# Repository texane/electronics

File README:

various electronic designs:
. dspic33f_board, a DSPIC33F based board, with CAN transceiver and serial over USB support via FTDI

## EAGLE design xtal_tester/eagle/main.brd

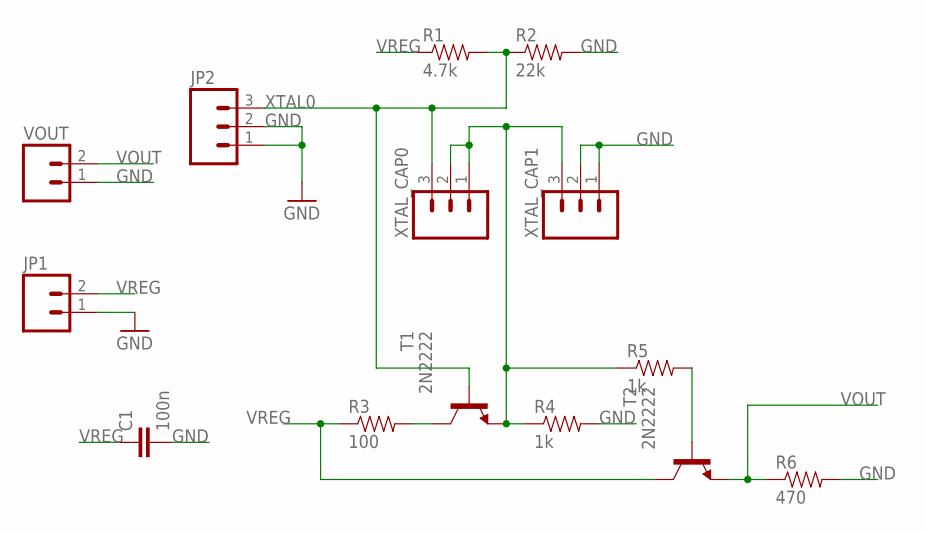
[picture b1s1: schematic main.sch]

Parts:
C1: 100n; CAP-PTH-SMALL
JP1: M02LOCK; 1X02_LOCK
JP2: M03LOCK; 1X03_LOCK
R1: 4.7k; AXIAL-0.4
R2: 22k; AXIAL-0.4
R3: 100; AXIAL-0.4
R4, R5: 1k; AXIAL-0.4
R6: 470; AXIAL-0.4
T1, T2: 2N2222; TO18
VOUT: M02LOCK; 1X02_LOCK
XTAL_CAP0, XTAL_CAP1: M03LOCK; 1X03_LOCK

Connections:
GND: C1.2, JP1.1, JP2.1, JP2.2, R2.P$2 (2), R4.P$2 (2), R6.P$2 (2), VOUT.1, XTAL_CAP1.1, XTAL_CAP1.2
unnamed: R5.P$2 (2), T2.2 (B)
unnamed: R3.P$2 (2), T1.3 (C)
unnamed: R4.P$1 (1), R5.P$1 (1), T1.1 (E), XTAL_CAP0.1, XTAL_CAP0.2, XTAL_CAP1.3
VOUT: R6.P$1 (1), T2.1 (E), VOUT.2
VREG: C1.1, JP1.2, R1.P$1 (1), R3.P$1 (1), T2.3 (C)
XTAL0: JP2.3, R1.P$2 (2), R2.P$1 (1), T1.2 (B), XTAL_CAP0.3

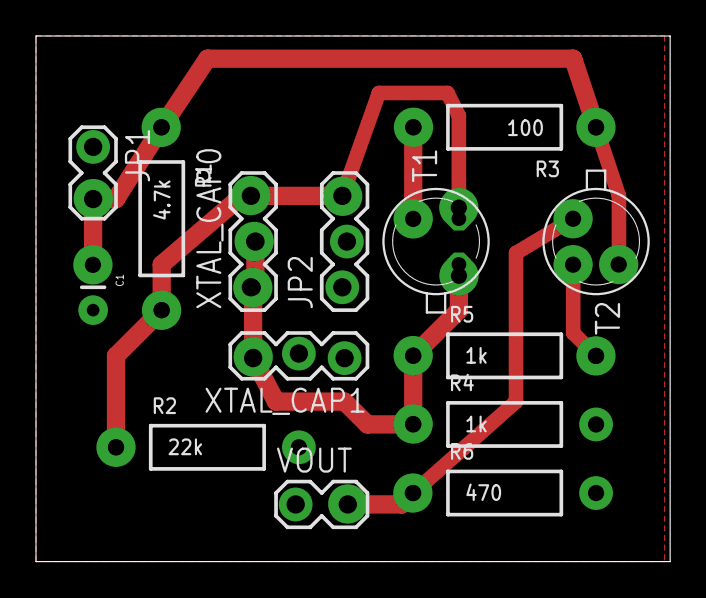
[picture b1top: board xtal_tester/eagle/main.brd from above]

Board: 2 copper layers, 35.2 x 29.2 mm, 14 parts (0 on the bottom side), 7 nets.

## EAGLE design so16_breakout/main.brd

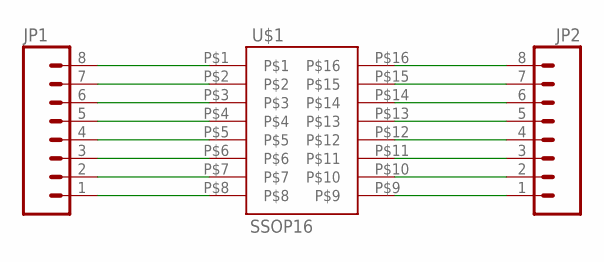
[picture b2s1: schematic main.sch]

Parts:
JP1, JP2: M08LONGPADS; 1X08_LONGPADS
U$1: SSOP16

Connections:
unnamed: JP1.8, U$1.P$1
unnamed: JP1.7, U$1.P$2
unnamed: JP1.6, U$1.P$3
unnamed: JP1.5, U$1.P$4
unnamed: JP1.4, U$1.P$5
unnamed: JP1.3, U$1.P$6
unnamed: JP1.2, U$1.P$7
unnamed: JP1.1, U$1.P$8
unnamed: JP2.8, U$1.P$16
unnamed: JP2.7, U$1.P$15
unnamed: JP2.6, U$1.P$14
unnamed: JP2.5, U$1.P$13
unnamed: JP2.4, U$1.P$12
unnamed: JP2.3, U$1.P$11
unnamed: JP2.2, U$1.P$10
unnamed: JP2.1, U$1.P$9

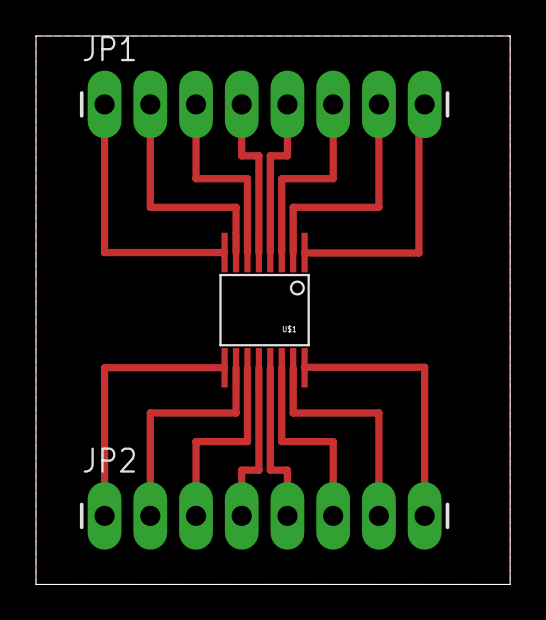
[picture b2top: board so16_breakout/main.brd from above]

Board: 2 copper layers, 26.3 x 30.5 mm, 3 parts (0 on the bottom side), 16 nets.

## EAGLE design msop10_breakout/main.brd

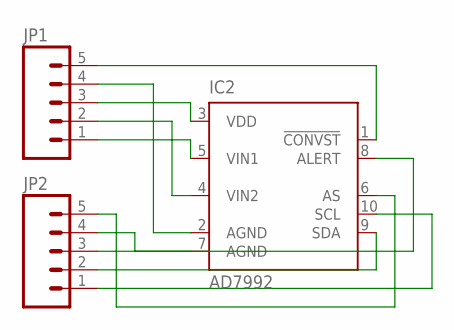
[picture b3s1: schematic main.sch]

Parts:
IC2: AD7992; MSOP10
JP1, JP2: M05PTH_LONGPADS; 1X05_LONGPADS

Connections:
unnamed: IC2.1 (!CONVST), JP1.5
unnamed: IC2.2 (AGND), JP1.4
unnamed: IC2.3 (VDD), JP1.3
unnamed: IC2.4 (VIN2), JP1.2
unnamed: IC2.5 (VIN1), JP1.1
unnamed: IC2.6 (AS), JP2.5
unnamed: IC2.7 (AGND), JP2.4
unnamed: IC2.8 (ALERT), JP2.3
unnamed: IC2.9 (SDA), JP2.2
unnamed: IC2.10 (SCL), JP2.1

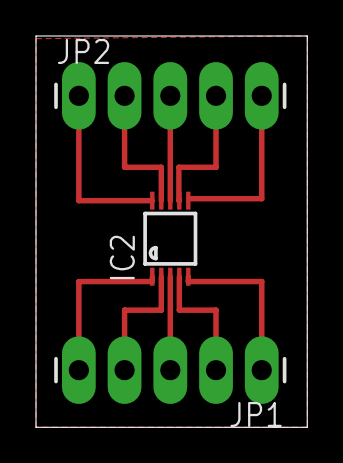
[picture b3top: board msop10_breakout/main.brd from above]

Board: 2 copper layers, 15.1 x 21.7 mm, 3 parts (0 on the bottom side), 10 nets.

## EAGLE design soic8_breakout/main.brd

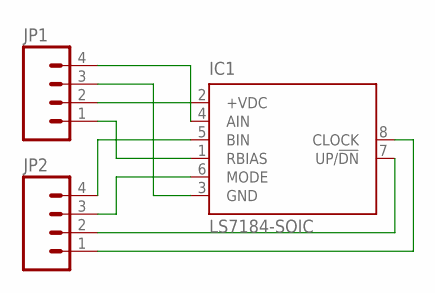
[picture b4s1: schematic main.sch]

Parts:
IC1: LS7184-SOIC; SOIC08
JP1, JP2: M04LONGPADS; 1X04_LONGPADS

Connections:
unnamed: IC1.1 (RBIAS), JP1.1
unnamed: IC1.2 (+VDC), JP1.2
unnamed: IC1.3 (GND), JP1.3
unnamed: IC1.4 (AIN), JP1.4
unnamed: IC1.5 (BIN), JP2.4
unnamed: IC1.6 (MODE), JP2.3
unnamed: IC1.7 (UP/!DN), JP2.2
unnamed: IC1.8 (CLOCK), JP2.1

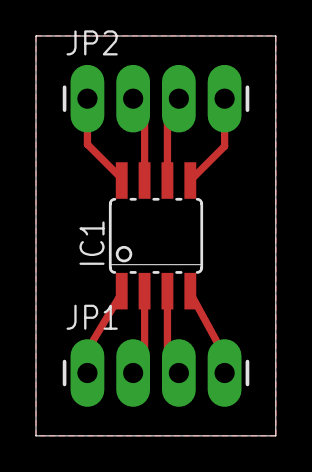
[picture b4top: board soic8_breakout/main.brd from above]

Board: 2 copper layers, 13.3 x 22.2 mm, 3 parts (0 on the bottom side), 8 nets.

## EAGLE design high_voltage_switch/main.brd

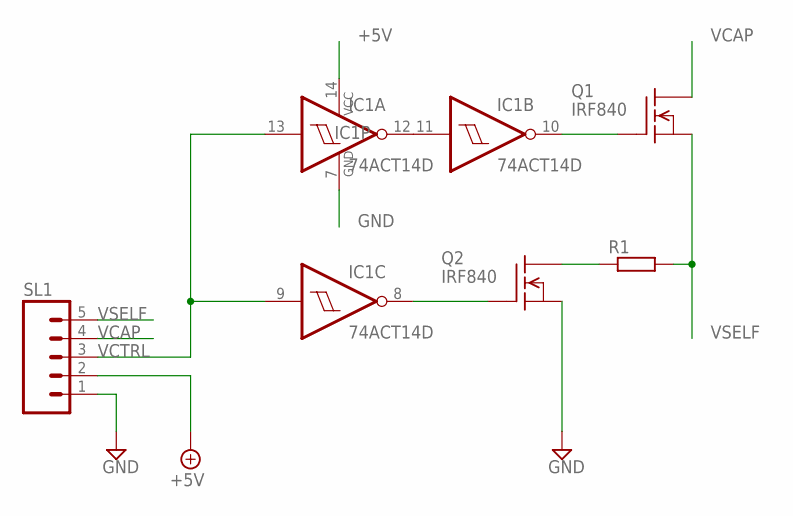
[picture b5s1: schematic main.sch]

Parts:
IC1: 74ACT14D; SO14
Q1, Q2: IRF840; TO220
R1: R-EU_0204/5; 0204/5
SL1: M05; 05P

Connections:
+5V: IC1.14 (VCC), SL1.2
GND: IC1.7 (GND), Q2.3 (S), SL1.1
unnamed: IC1.11 (I), IC1.12 (O)
unnamed: IC1.8 (O), Q2.1 (G)
unnamed: IC1.10 (O), Q1.1 (G)
unnamed: Q2.2 (D), R1.1
VCAP: Q1.2 (D), SL1.4
VCTRL: IC1.9 (I), IC1.13 (I), SL1.3
VSELF: Q1.3 (S), R1.2, SL1.5

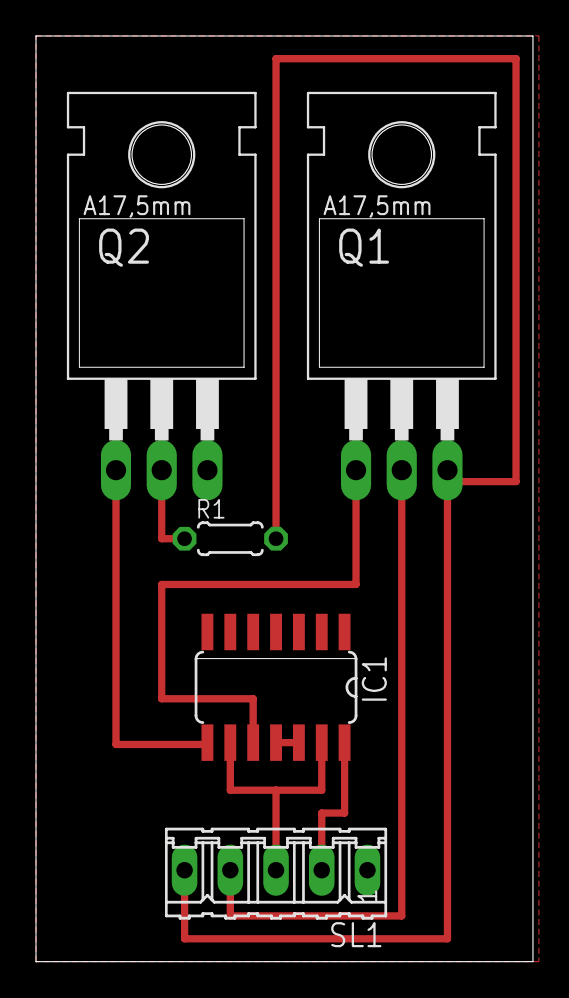
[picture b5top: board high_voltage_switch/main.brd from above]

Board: 2 copper layers, 27.6 x 51.4 mm, 5 parts (0 on the bottom side), 9 nets.

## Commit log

2011-11-18 [add] dspic33f_board
2011-11-18 [update] README
2011-11-18 [add] main.pdf
2011-11-19 [update] dspic33f_board ealge schematics
2011-11-19 [add] notes
2011-11-19 [update, dspic33f_board] add power switch, standoff holes, power leds
2011-11-19 [update, dspic33f_board] use only one CAN doubling the pins
2011-11-19 . add voltage regulator name . remove ft232 oscillator . document the OUTPUT only voltage connector . remove the CAN slope control 10k resistor . add CAN terminal resistor jumper . correct LED resist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
2011-11-19 [fix] use TTL IOs to interface with MCP2551
2011-11-19 [fix] CAN terminal resistor is 120 ohms
2011-11-19 [update] start routing
2011-11-19 [wip] dspic33f_baord routing
2011-11-19 [wip] dspic33f_board routing
2011-11-19 [wip] dspic33f_board routing
2011-11-19 [add] dspic33f_board, main_routed.pdf
2011-11-20 [add] main_airwire.pdf
2011-11-20 [wip] dpic33f_board, not routed but placed
2011-11-20 [wip] dpic33f_board, routed
2011-11-20 [rename] dspic33f_board, main.pdf to main_schematics.pdf
2011-11-20 [update] simplify, remove one connector
2011-11-20 [update] routed
2011-11-22 [wip] simplify routing
2011-11-22 [wip] routing
2011-11-23 [add] dspic33f_board bom
2011-11-25 [add] dspic33f_board_nerick
2011-11-25 [add] dspic33f_board_nerick, schematics and board pdfs
2011-11-27 [add] dspic33f_baord_rerouted
2011-11-27 [update] dspic33f_baord_rerouted
2011-11-27 [add] dspic33f board, ground plane
2011-11-27 [add] dspic33f board, ground plane, main_sch.pdf
2011-12-03 [update, fix] dspic33f_board overlap
2011-12-03 [update] sent to pcb-pool
2011-12-31 [add] dspic33f_board_source
2011-12-31 [update] dspi33f_board_source, remove interrupt disabling
2012-01-02 [update] add CAN test
2012-01-03 [add] igreloader, device/main.c
2012-01-03 [update] igreloader flash programming routines
2012-01-03 [update] igreload, flash programming
2012-01-03 [add] igreloader, host/main.c
2012-01-03 [add] igreloader, host script do_build.sh
2012-01-03 [fix] igreloader, make hex.c compile
2012-01-03 [add] igreloader, main.hex example
2012-01-03 [fix] igreloader, hex reader ok
2012-01-03 [update] igreloader, hex reader
2012-01-03 [update] igreloader, hex device programming routine
2012-01-03 [update] igreloader, TODOS
2012-01-03 [fix] igreloader, unaligned page
2012-01-03 [wip] igreloader
2012-01-03 [fix] igreloader, do_program test routine
2012-03-12 [update]
2012-03-12 [add]
2012-04-01 [ add ] high voltage switch
2012-04-02 [ add ] so16_breakout
2012-04-02 [ add ] soic8 breakout
2012-04-02 [ add ] notes
2012-04-02 [ add ] msop10_breakout
2012-04-02 [ update ] so16_breakout
2012-04-12 [ add ] sot23_breakout
2012-04-12 [ update ] notes, bordering
2012-04-13 [ add ] msop10_breakout.dil
2012-04-14 [ add ] pcb_etching notes, toner transfer method
2012-04-14 [ update ] pcb_etching notes
2012-04-15 [ update ] pcb_etching/notes
2012-09-03 [ update ] pcb etching notes
2012-09-05 [ add ] xtal_tester

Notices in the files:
parts and their libraries:
SparkFun: Licensing: CC v3.0 Share-Alike You are welcome to use this library for commercial purposes.
